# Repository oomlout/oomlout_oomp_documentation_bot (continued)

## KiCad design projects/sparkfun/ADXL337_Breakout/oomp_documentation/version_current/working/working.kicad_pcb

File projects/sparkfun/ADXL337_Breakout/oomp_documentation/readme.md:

# None

## Description
None/
## Schematic

## Bill of Materials
| Id | Designator | Footprint | Quantity | Designation | Supplier and ref |  |
| --- | --- | --- | --- | --- | --- | --- |
| 1 | C4 | 0603-CAP | 1 | 0.1uF |  |  |
| 2 | FID1,FID2 | FIDUCIAL-1X2 | 2 | FIDUCIAL1X2 |  |  |
| 3 | FRAME1 | CREATIVE_COMMONS | 1 | FRAME-LETTER |  |  |
| 4 | LOGO1 | SFE_LOGO_FLAME_.1 | 1 | SFE_LOGO_FLAME.1_INC<br>H |  |  |
| 5 | C3,C1,C2 | 0603-CAP | 3 | 10nF |  |  |
| 6 | JP1 | 1X06 | 1 |  |  |  |
| 7 | STANDOFF1 | STAND-OFF | 1 | STAND-OFF |  |  |
| 8 | U1 | LFCSP_LQ-16 | 1 | ADXL337 |  |  |
| 9 | LOGO3 | SFE_LOGO_NAME_FLAME_<br>.1 | 1 | SFE_LOGO_NAME_FLAME.<br>1_INCH |  |  |
| 10 | LOGO2 | OSHW-LOGO-S | 1 | OSHW-LOGOS |  |  |

## Images

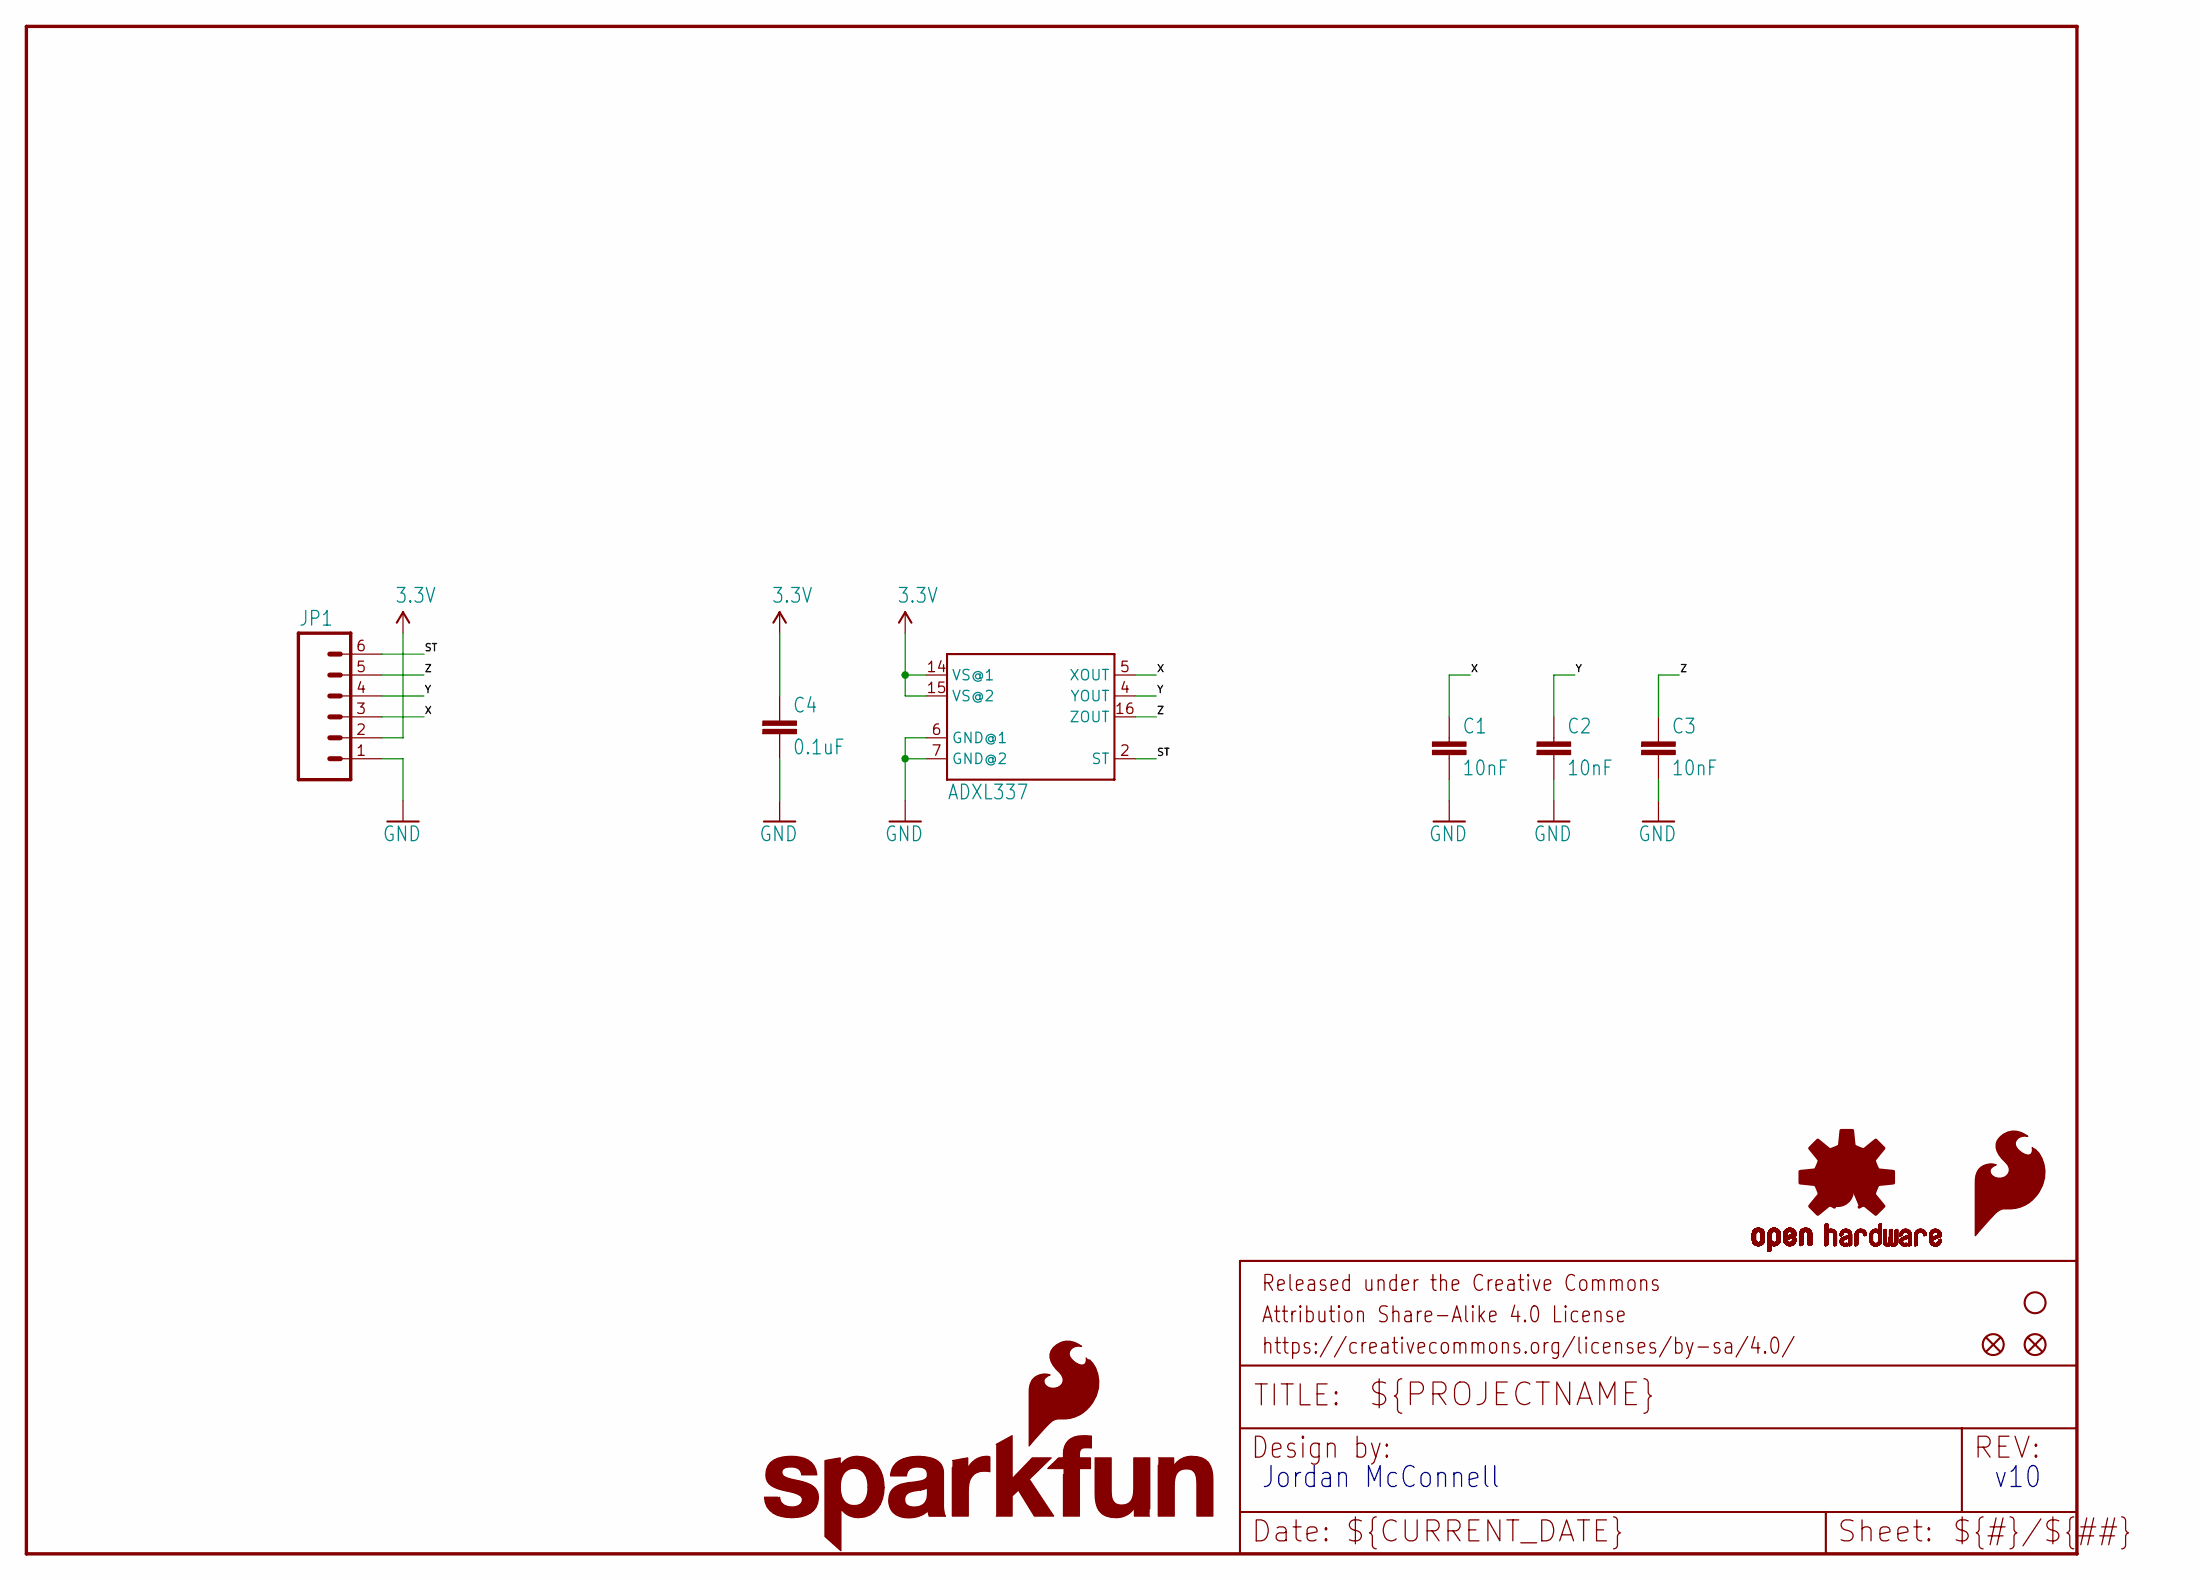
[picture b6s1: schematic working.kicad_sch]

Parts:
C1, C2, C3: 10nF; 0603-CAP
C4: 0.1uF; 0603-CAP
FID1, FID2: FIDUCIAL1X2; FIDUCIAL-1X2
FRAME1: FRAME-LETTER; CREATIVE_COMMONS
JP1: M06SIP; 1X06
LOGO1: SFE_LOGO_FLAME.1_INCH; SFE_LOGO_FLAME_.1
LOGO2: OSHW-LOGOS; OSHW-LOGO-S
LOGO3: SFE_LOGO_NAME_FLAME.1_INCH; SFE_LOGO_NAME_FLAME_.1
STANDOFF1: STAND-OFF
U1: ADXL337; LFCSP_LQ-16

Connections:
3.3V: C4.1, JP1.2, U1.14 (VS@1), U1.15 (VS@2)
GND: C1.2, C2.2, C3.2, C4.2, JP1.1, U1.6 (GND@1), U1.7 (GND@2)
ST: JP1.6, U1.2 (ST)
X: C1.1, JP1.3, U1.5 (XOUT)
Y: C2.1, JP1.4, U1.4 (YOUT)
Z: C3.1, JP1.5, U1.16 (ZOUT)

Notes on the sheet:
Jordan McConnell
v10

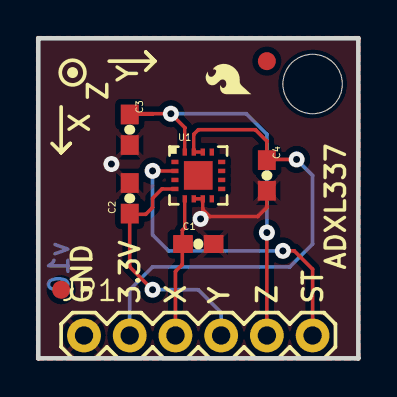
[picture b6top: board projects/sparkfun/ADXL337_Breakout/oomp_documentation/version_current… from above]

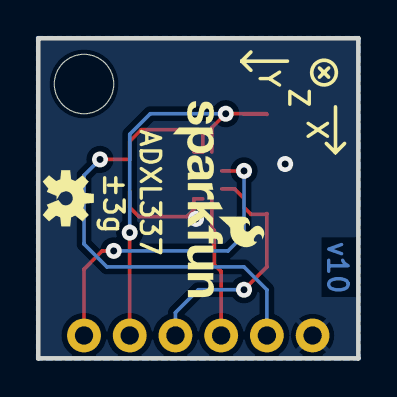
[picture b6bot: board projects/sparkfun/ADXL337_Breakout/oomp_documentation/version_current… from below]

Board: 2 copper layers, 17.8 x 17.8 mm, 13 parts (2 on the bottom side), 6 nets.

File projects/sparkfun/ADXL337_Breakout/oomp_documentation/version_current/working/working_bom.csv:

"Id";"Designator";"Footprint";"Quantity";"Designation";"Supplier and ref";
1;"C4";"0603-CAP";1;"0.1uF";;;
2;"FID1,FID2";"FIDUCIAL-1X2";2;"FIDUCIAL1X2";;;
3;"FRAME1";"CREATIVE_COMMONS";1;"FRAME-LETTER";;;
4;"LOGO1";"SFE_LOGO_FLAME_.1";1;"SFE_LOGO_FLAME.1_INCH";;;
5;"C3,C1,C2";"0603-CAP";3;"10nF";;;
6;"JP1";"1X06";1;"";;;
7;"STANDOFF1";"STAND-OFF";1;"STAND-OFF";;;
8;"U1";"LFCSP_LQ-16";1;"ADXL337";;;
9;"LOGO3";"SFE_LOGO_NAME_FLAME_.1";1;"SFE_LOGO_NAME_FLAME.1_INCH";;;
10;"LOGO2";"OSHW-LOGO-S";1;"OSHW-LOGOS";;;

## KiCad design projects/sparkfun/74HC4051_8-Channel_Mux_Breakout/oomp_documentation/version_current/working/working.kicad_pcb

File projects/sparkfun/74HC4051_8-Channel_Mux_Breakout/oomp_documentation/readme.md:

# None

## Description
None/
## Schematic

## Bill of Materials
| Id | Designator | Footprint | Quantity | Designation | Supplier and ref |  |
| --- | --- | --- | --- | --- | --- | --- |
| 1 | LOGO2 | OSHW-LOGO-MINI | 1 | OSHW-LOGOMINI |  |  |
| 2 | U1 | DHVQFN-16-2.5X3.5MM | 1 |  |  |  |
| 3 | LOGO1 | SFE_LOGO_FLAME_.1 | 1 | SFE_LOGO_FLAME.1_INC<br>H |  |  |
| 4 | R1 | 0603 | 1 | 10k |  |  |
| 5 | H2,H1 | STAND-OFF | 2 | STAND-OFF |  |  |
| 6 | C1 | 0603 | 1 | 0.1uF |  |  |
| 7 | FD2,FD1 | FIDUCIAL-1X2 | 2 | FIDUCIAL1X2 |  |  |
| 8 | JP1 | PAD-JUMPER-2-NC_BY_P<br>ASTE_NO_SILK | 1 | VEE-GND |  |  |
| 9 | FRAME1 | CREATIVE_COMMONS | 1 | FRAME-LETTER |  |  |
| 10 | J1 | 1X11 | 1 |  |  |  |
| 11 | LOGO3 | SFE_LOGO_NAME_.1 | 1 | SFE_LOGO_NAME.1_INCH |  |  |
| 12 | J2 | 1X08_ROUND | 1 |  |  |  |

## Images

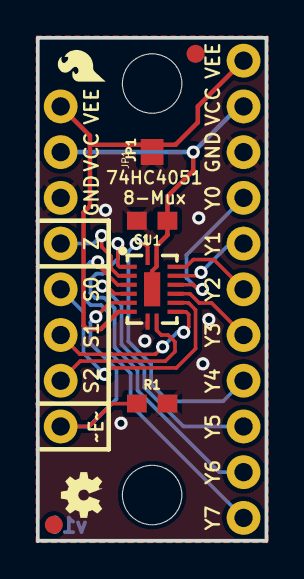
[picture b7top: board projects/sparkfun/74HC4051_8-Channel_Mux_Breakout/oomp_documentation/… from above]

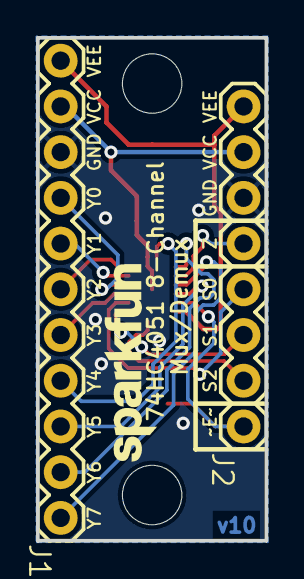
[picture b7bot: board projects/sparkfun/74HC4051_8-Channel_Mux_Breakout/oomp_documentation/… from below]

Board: 2 copper layers, 12.7 x 27.9 mm, 14 parts (3 on the bottom side), 16 nets.

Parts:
C1: 0.1uF; 0603
FD1, FD2: FIDUCIAL1X2; FIDUCIAL-1X2
FRAME1: FRAME-LETTER; CREATIVE_COMMONS
H1, H2: STAND-OFF
J1: 1X11
J2: 1X08_ROUND
JP1: VEE-GND; PAD-JUMPER-2-NC_BY_PASTE_NO_SILK
LOGO1: SFE_LOGO_FLAME.1_INCH; SFE_LOGO_FLAME_.1
LOGO2: OSHW-LOGOMINI; OSHW-LOGO-MINI
LOGO3: SFE_LOGO_NAME.1_INCH; SFE_LOGO_NAME_.1
R1: 10k; 0603
U1: DHVQFN-16-2.5X3.5MM

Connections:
GND: C1.2, J1.9, J2.6, JP1.1, R1.2, U1.8
S0: J2.4, U1.11
S1: J2.3, U1.10
S2: J2.2, U1.9
VCC: C1.1, J1.10, J2.7, U1.16, U1.EP
VEE: J1.11, J2.8, JP1.2, U1.7
Y0: J1.8, U1.13
Y1: J1.7, U1.14
Y2: J1.6, U1.15
Y3: J1.5, U1.12
Y4: J1.4, U1.1
Y5: J1.3, U1.5
Y6: J1.2, U1.2
Y7: J1.1, U1.4
Z: J2.5, U1.3
~E: J2.1, R1.1, U1.6

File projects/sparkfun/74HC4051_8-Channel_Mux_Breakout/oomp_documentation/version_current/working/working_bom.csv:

"Id";"Designator";"Footprint";"Quantity";"Designation";"Supplier and ref";
1;"LOGO2";"OSHW-LOGO-MINI";1;"OSHW-LOGOMINI";;;
2;"U1";"DHVQFN-16-2.5X3.5MM";1;"";;;
3;"LOGO1";"SFE_LOGO_FLAME_.1";1;"SFE_LOGO_FLAME.1_INCH";;;
4;"R1";"0603";1;"10k";;;
5;"H2,H1";"STAND-OFF";2;"STAND-OFF";;;
6;"C1";"0603";1;"0.1uF";;;
7;"FD2,FD1";"FIDUCIAL-1X2";2;"FIDUCIAL1X2";;;
8;"JP1";"PAD-JUMPER-2-NC_BY_PASTE_NO_SILK";1;"VEE-GND";;;
9;"FRAME1";"CREATIVE_COMMONS";1;"FRAME-LETTER";;;
10;"J1";"1X11";1;"";;;
11;"LOGO3";"SFE_LOGO_NAME_.1";1;"SFE_LOGO_NAME.1_INCH";;;
12;"J2";"1X08_ROUND";1;"";;;

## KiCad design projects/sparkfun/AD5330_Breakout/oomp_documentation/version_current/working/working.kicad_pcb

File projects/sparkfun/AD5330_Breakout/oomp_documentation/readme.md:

# None

## Description
None/
## Schematic

## Bill of Materials
| Id | Designator | Footprint | Quantity | Designation | Supplier and ref |  |
| --- | --- | --- | --- | --- | --- | --- |
| 1 | C2 | EIA3216 | 1 | 10uF |  |  |
| 2 | JP6 | 1X08 | 1 |  |  |  |
| 3 | JP8,JP9 | 1X02 | 2 |  |  |  |
| 4 | JP2,JP3 | FIDUCIAL-1X2 | 2 | FIDUCIAL1X2 |  |  |
| 5 | FRAME1 | CREATIVE_COMMONS | 1 | FRAME-LETTER |  |  |
| 6 | C1 | 0603-CAP | 1 | 0.1uF |  |  |
| 7 | LOGO1 | OSHW-LOGO-S | 1 | OSHW-LOGOS |  |  |
| 8 | JP7 | 1X07 | 1 |  |  |  |
| 9 | U1 | TSSOP20 | 1 | AD5330 |  |  |
| 10 | JP1 | SFE-NEW-WEBLOGO | 1 | LOGO-SFENEW |  |  |

## Images

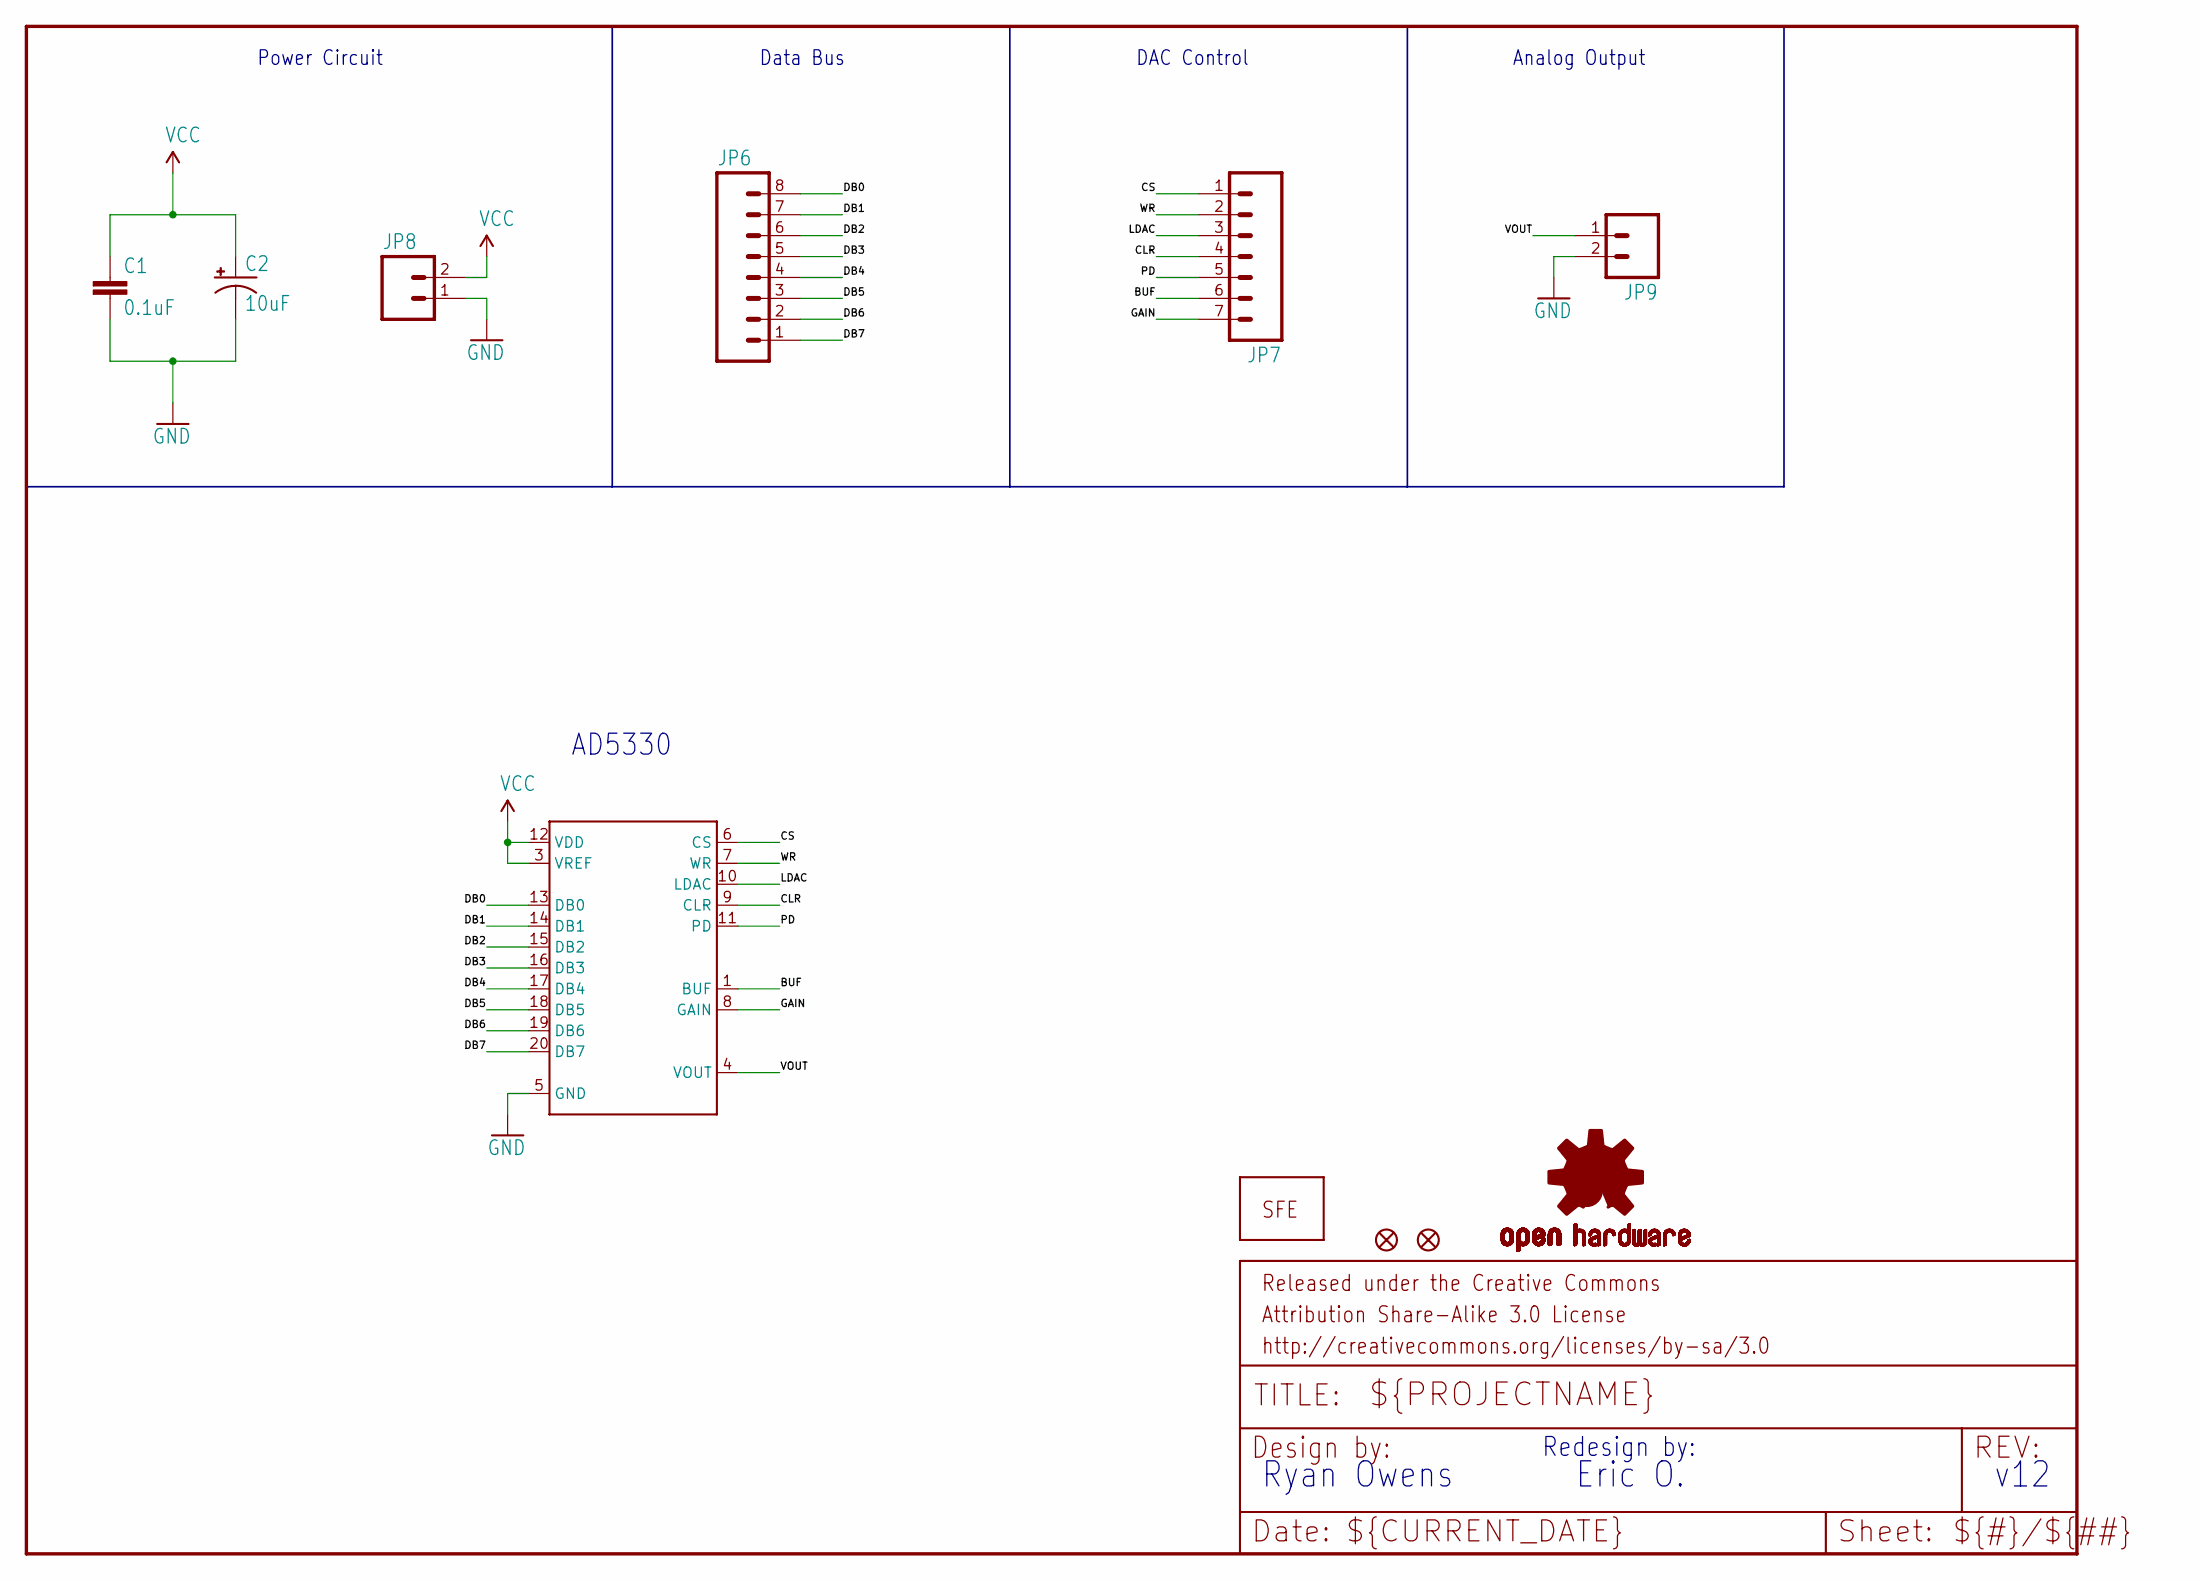
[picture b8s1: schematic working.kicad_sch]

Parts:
C1: 0.1uF; 0603-CAP
C2: 10uF; EIA3216
FRAME1: FRAME-LETTER; CREATIVE_COMMONS
JP1: LOGO-SFENEW; SFE-NEW-WEBLOGO
JP2, JP3: FIDUCIAL1X2; FIDUCIAL-1X2
JP6: M08; 1X08
JP7: M07; 1X07
JP8, JP9: M02PTH; 1X02
LOGO1: OSHW-LOGOS; OSHW-LOGO-S
U1: AD5330; TSSOP20

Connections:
BUF: JP7.6, U1.1 (BUF)
CLR: JP7.4, U1.9 (CLR)
CS: JP7.1, U1.6 (CS)
DB0: JP6.8, U1.13 (DB0)
DB1: JP6.7, U1.14 (DB1)
DB2: JP6.6, U1.15 (DB2)
DB3: JP6.5, U1.16 (DB3)
DB4: JP6.4, U1.17 (DB4)
DB5: JP6.3, U1.18 (DB5)
DB6: JP6.2, U1.19 (DB6)
DB7: JP6.1, U1.20 (DB7)
GAIN: JP7.7, U1.8 (GAIN)
GND: C1.2, C2.C (-), JP8.1, JP9.2, U1.5 (GND)
LDAC: JP7.3, U1.10 (LDAC)
PD: JP7.5, U1.11 (PD)
VCC: C1.1, C2.A (+), JP8.2, U1.3 (VREF), U1.12 (VDD)
VOUT: JP9.1, U1.4 (VOUT)
WR: JP7.2, U1.7 (WR)

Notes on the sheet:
Ryan Owens
Eric O.
Analog Output
v12
Redesign by:
DAC Control
AD5330
Power Circuit
Data Bus

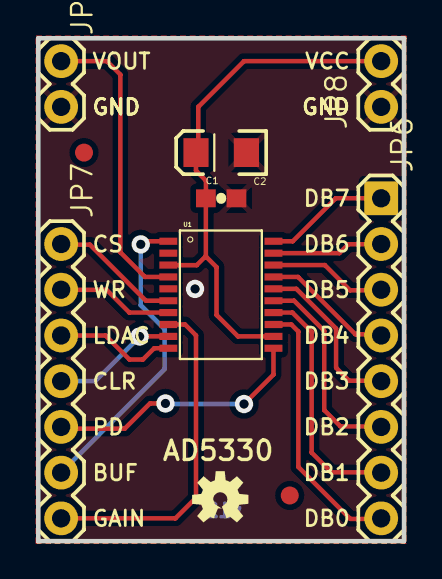
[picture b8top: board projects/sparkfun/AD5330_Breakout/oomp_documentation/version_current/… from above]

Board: 2 copper layers, 20.3 x 27.9 mm, 12 parts (1 on the bottom side), 18 nets.

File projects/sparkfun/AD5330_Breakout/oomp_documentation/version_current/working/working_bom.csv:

"Id";"Designator";"Footprint";"Quantity";"Designation";"Supplier and ref";
1;"C2";"EIA3216";1;"10uF";;;
2;"JP6";"1X08";1;"";;;
3;"JP8,JP9";"1X02";2;"";;;
4;"JP2,JP3";"FIDUCIAL-1X2";2;"FIDUCIAL1X2";;;
5;"FRAME1";"CREATIVE_COMMONS";1;"FRAME-LETTER";;;
6;"C1";"0603-CAP";1;"0.1uF";;;
7;"LOGO1";"OSHW-LOGO-S";1;"OSHW-LOGOS";;;
8;"JP7";"1X07";1;"";;;
9;"U1";"TSSOP20";1;"AD5330";;;
10;"JP1";"SFE-NEW-WEBLOGO";1;"LOGO-SFENEW";;;

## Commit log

2023-07-22 readme fix
2023-07-22 readme test
2023-07-22 moved readme
2023-07-22 readme relative test
2023-07-22 added another project
2023-07-23 checking generations
2023-07-23 current state
2023-07-23 run through
2023-07-25 some documentation
2023-07-26 test
2023-07-26 commit of current state
